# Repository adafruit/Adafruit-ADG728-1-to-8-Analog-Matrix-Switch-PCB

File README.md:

## Adafruit ADG728 1-to-8 Analog Matrix Switch - Stemma QT PCB

<a href="http://www.adafruit.com/products/5899"><br/>
Click here to purchase one from the Adafruit shop</a>

PCB files for the Adafruit ADG728 1-to-8 Analog Matrix Switch - Stemma QT. 

Format is EagleCAD schematic and board layout
* https://www.adafruit.com/product/5899

### Description

Analog switches are a solid state alternative to relays, when you want a smaller, lower-power technology that won't wear out mechanically. And, as the name implies, you can use the Adafruit ADG728 1-to-8 Analog Matrix Switch to connect between eight analog signals, much like a set of 8 mechanical switches. These chips tend to be tiny surface mount parts, so this breakout will let anyone use the ADG728 switch for signals up to 5V, without fiddly soldering.

The ADG728 uses I2C to select which of the 8 channels switches to turn on or off, to connect that channel to the single analog 'D' pin Note that unlike digital switches and multiplexers, these are not 'input' and 'output' because the signal is bidirectional. You could have the D signal be an input to 8 outputs, or the 8 inputs to one output.

Also, the ADG728 isn't really a 'selecting multiplexer', its a matrix switch with 8 independent switches. That means that yes, you could treat it like an SP8T where you select which signal is routed to the D pin, you can also turn on multiple switches to 'merge' the signals together. 

Unlike a relay or mechanical switch, analog switches don't wear out, and the switch time is near instant, about 100nS. The ADG728 chip also guarantees break-before-make so the deselected switches will open before selected switches close.

However, there's a few things to watch out for:

* The VIN power pin (the red wire if using a STEMMA QT cable) must as high as the highest analog voltages you want to switch. That means if the analog signals are no more than 5VDC, the V+ pin must be higher than 5V. You cannot power this pin with 3.3V and switch 5V signals.
* It cannot switch signals below ground. No negative voltages can be applied to the Switch or D pins!
* Analog switches are for signals, not power! Since this is not a mechanical switch, the signals pass through circuitry that is not designed to source or sink current. This is great for analog signal voltages, and is not good for providing more than a few mA of current.

In addition to the 8 switch S pins and the D pin that can be switched to, there's also two I2C address pins so you can change the default address from 0x4C up to 0x4F. There's also a reset pin if you want to immediately set all the switches to open.

To get you going fast, we spun up a custom-made PCB in the STEMMA QT form factor, making it easy to interface with. The STEMMA QT connectors on either side are compatible with the SparkFun Qwiic I2C connectors. This allows you to make solderless connections between your development board and the ADG or to chain it with a wide range of other sensors and accessories using a compatible cable.

### License

Adafruit invests time and resources providing this open source design, please support Adafruit and open-source hardware by purchasing products from [Adafruit](https://www.adafruit.com)!

Designed by Limor Fried/Ladyada for Adafruit Industries.

Creative Commons Attribution/Share-Alike, all text above must be included in any redistribution. 
See license.txt for additional details.

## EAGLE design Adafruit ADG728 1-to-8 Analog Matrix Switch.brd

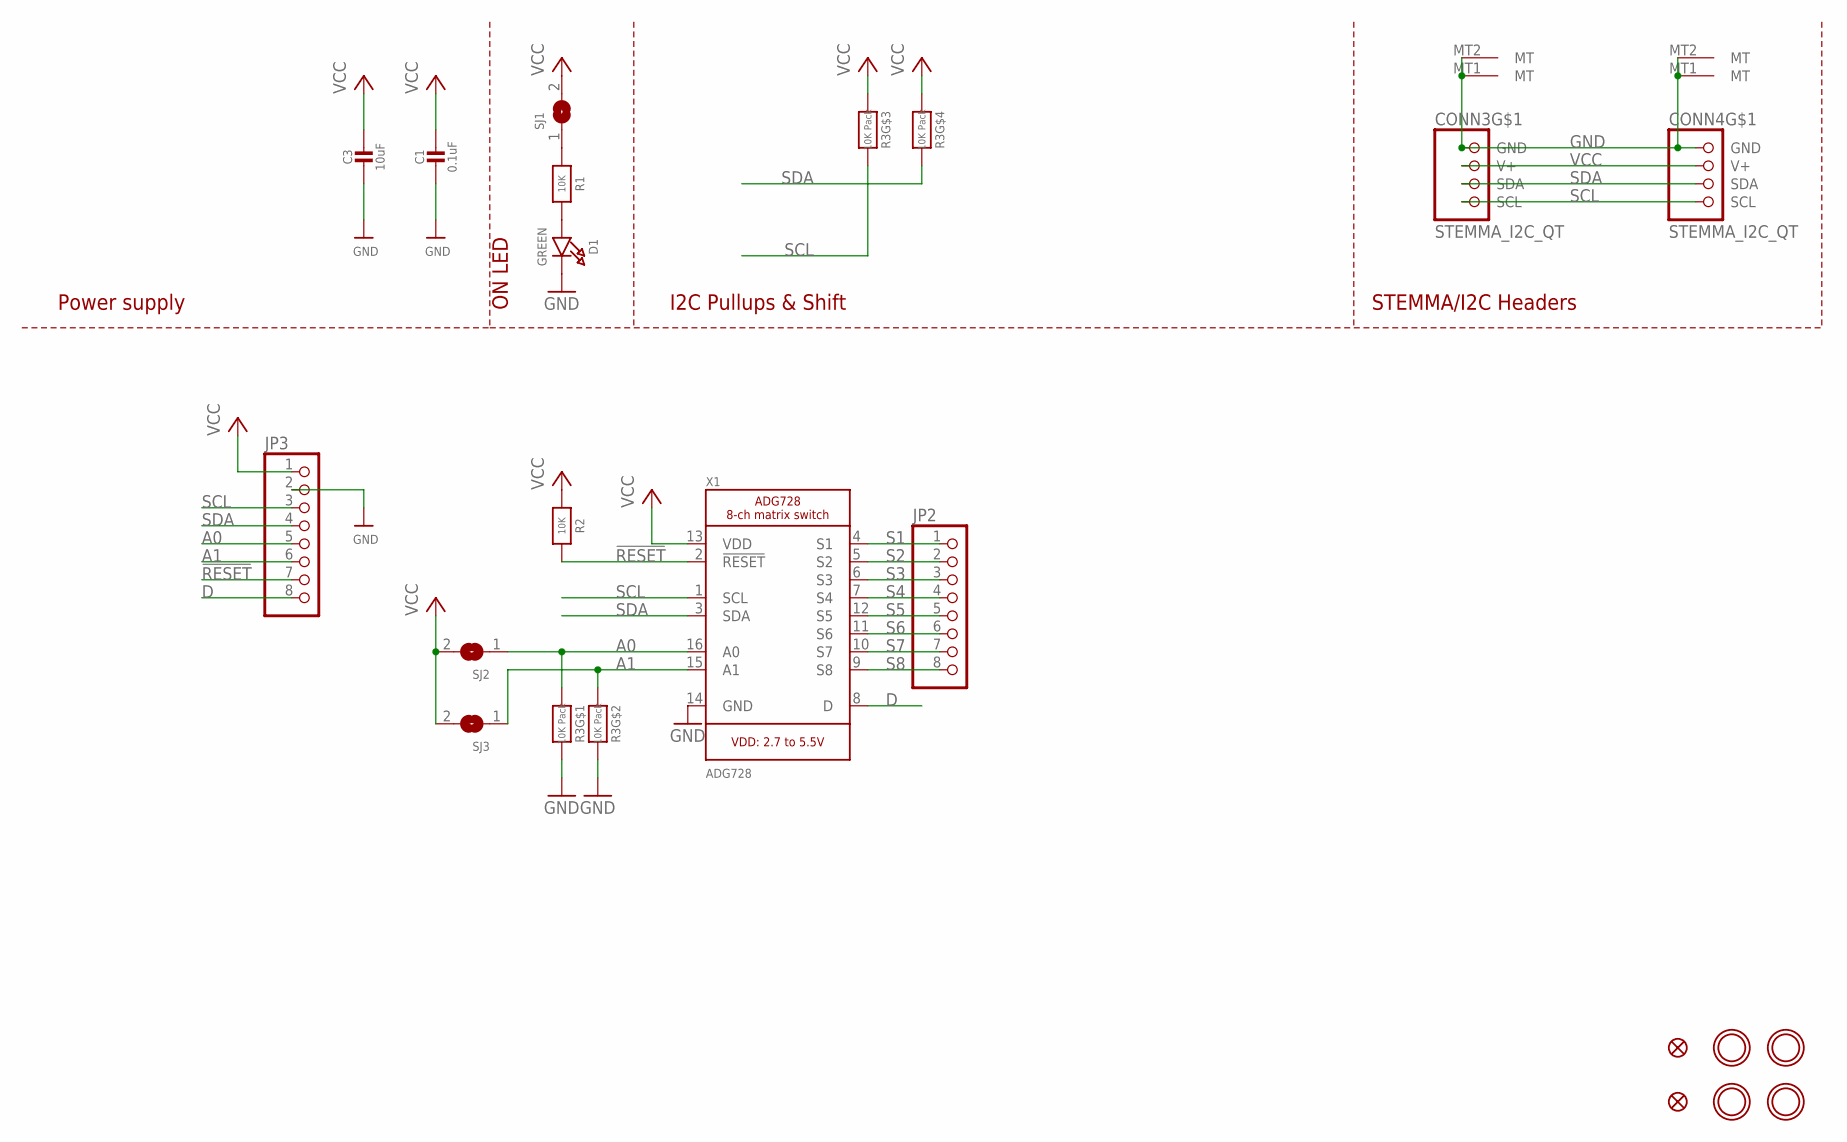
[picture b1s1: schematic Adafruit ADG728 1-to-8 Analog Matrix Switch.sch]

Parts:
C1: 0.1uF; 0603-NO
C3: 10uF; 0805-NO
CONN3, CONN4: STEMMA_I2C_QT; JST_SH4
D1: GREEN; CHIPLED_0603_NOOUTLINE
FID3, FID4: FIDUCIAL_1MM
JP2, JP3: HEADER-1X870MIL; 1X08_ROUND_70
R1, R2: 10K; 0603-NO
R3: 10K Pack; RESPACK_4X0603
SJ1: SOLDERJUMPERCLOSED; SOLDERJUMPER_CLOSEDWIRE
SJ2, SJ3: SOLDERJUMPER; SOLDERJUMPER_ARROW_NOPASTE
U$1, U$17, U$19, U$21: MOUNTINGHOLE2.5; MOUNTINGHOLE_2.5_PLATED
X1: ADG728; TSSOP16

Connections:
!RESET: JP3.7, R2.2, X1.2 (!RESET)
A0: JP3.5, R3.1, SJ2.1, X1.16 (A0)
A1: JP3.6, R3.2 (1), SJ3.1, X1.15 (A1)
D: JP3.8, X1.8 (D)
GND: C1.2, C3.2, CONN3.1 (GND), CONN3.MT1 (MT), CONN3.MT2 (MT), CONN4.1 (GND), CONN4.MT1 (MT), CONN4.MT2 (MT), D1.C, JP3.2, R3.7 (2), R3.8 (2), X1.14 (GND)
unnamed: D1.A, R1.2
unnamed: R1.1, SJ1.1
S1: JP2.1, X1.4 (S1)
S2: JP2.2, X1.5 (S2)
S3: JP2.3, X1.6 (S3)
S4: JP2.4, X1.7 (S4)
S5: JP2.5, X1.12 (S5)
S6: JP2.6, X1.11 (S6)
S7: JP2.7, X1.10 (S7)
S8: JP2.8, X1.9 (S8)
SCL: CONN3.4 (SCL), CONN4.4 (SCL), JP3.3, R3.6 (2), X1.1 (SCL)
SDA: CONN3.3 (SDA), CONN4.3 (SDA), JP3.4, R3.5 (2), X1.3 (SDA)
VCC: C1.1, C3.1, CONN3.2 (V+), CONN4.2 (V+), JP3.1, R2.1, R3.3 (1), R3.4 (1), SJ1.2, SJ2.2, SJ3.2, X1.13 (VDD)

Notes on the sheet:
I2C Pullups & Shift
STEMMA/I2C Headers
ON LED
Power supply

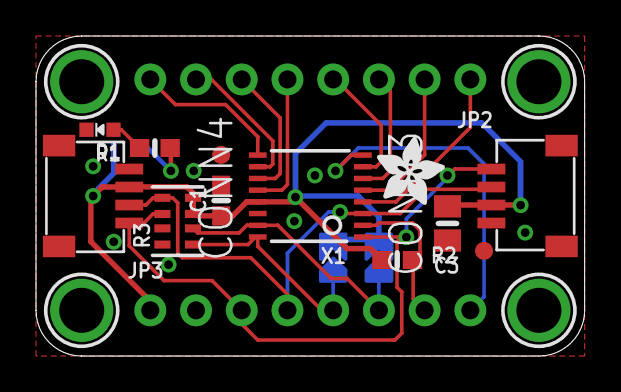
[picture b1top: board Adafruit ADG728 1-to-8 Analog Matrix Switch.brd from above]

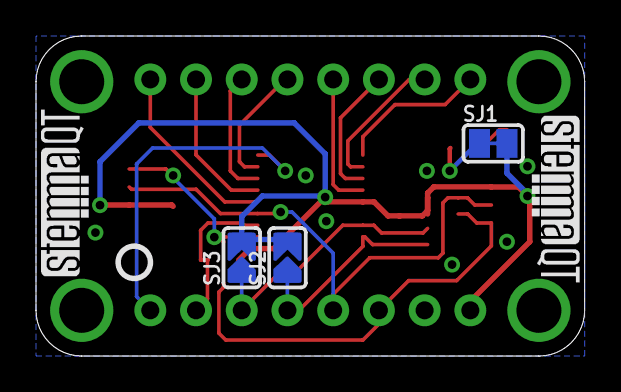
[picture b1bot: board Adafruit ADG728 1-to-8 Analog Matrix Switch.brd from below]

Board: 2 copper layers, 30.5 x 17.8 mm, 48 parts (12 on the bottom side), 18 nets.

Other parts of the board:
PLABEL0: PLABEL0
PLABEL1: PLABEL1
PLABEL2: PLABEL2
PLABEL3: PLABEL3
PLABEL4: PLABEL4
PLABEL5: PLABEL5
PLABEL6: PLABEL6
PLABEL7: PLABEL7
PLABEL8: PLABEL8
PLABEL9: PLABEL9
PLABEL10: PLABEL10
PLABEL11: PLABEL11
PLABEL12: PLABEL12
PLABEL13: PLABEL13
PLABEL14: PLABEL14
PLABEL15: PLABEL15
PLABEL16: PLABEL16
PLABEL17: PLABEL17
PLABEL18: PLABEL18
PLABEL19: PLABEL19
PLABEL20: PLABEL20
PLABEL21: PLABEL21
PLABEL22: PLABEL22
PLABEL23: PLABEL23
U$22: ADAFRUIT_3.5MM
U$25: PCBFEAT-REV-040
U$30, U$31: STEMMAQT

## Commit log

2024-04-10 cookiecutter

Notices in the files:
parts and their libraries:
microbuilder: This work is placed in the public domain, and may be freely used for commercial and non-commercial work with the following conditions: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
